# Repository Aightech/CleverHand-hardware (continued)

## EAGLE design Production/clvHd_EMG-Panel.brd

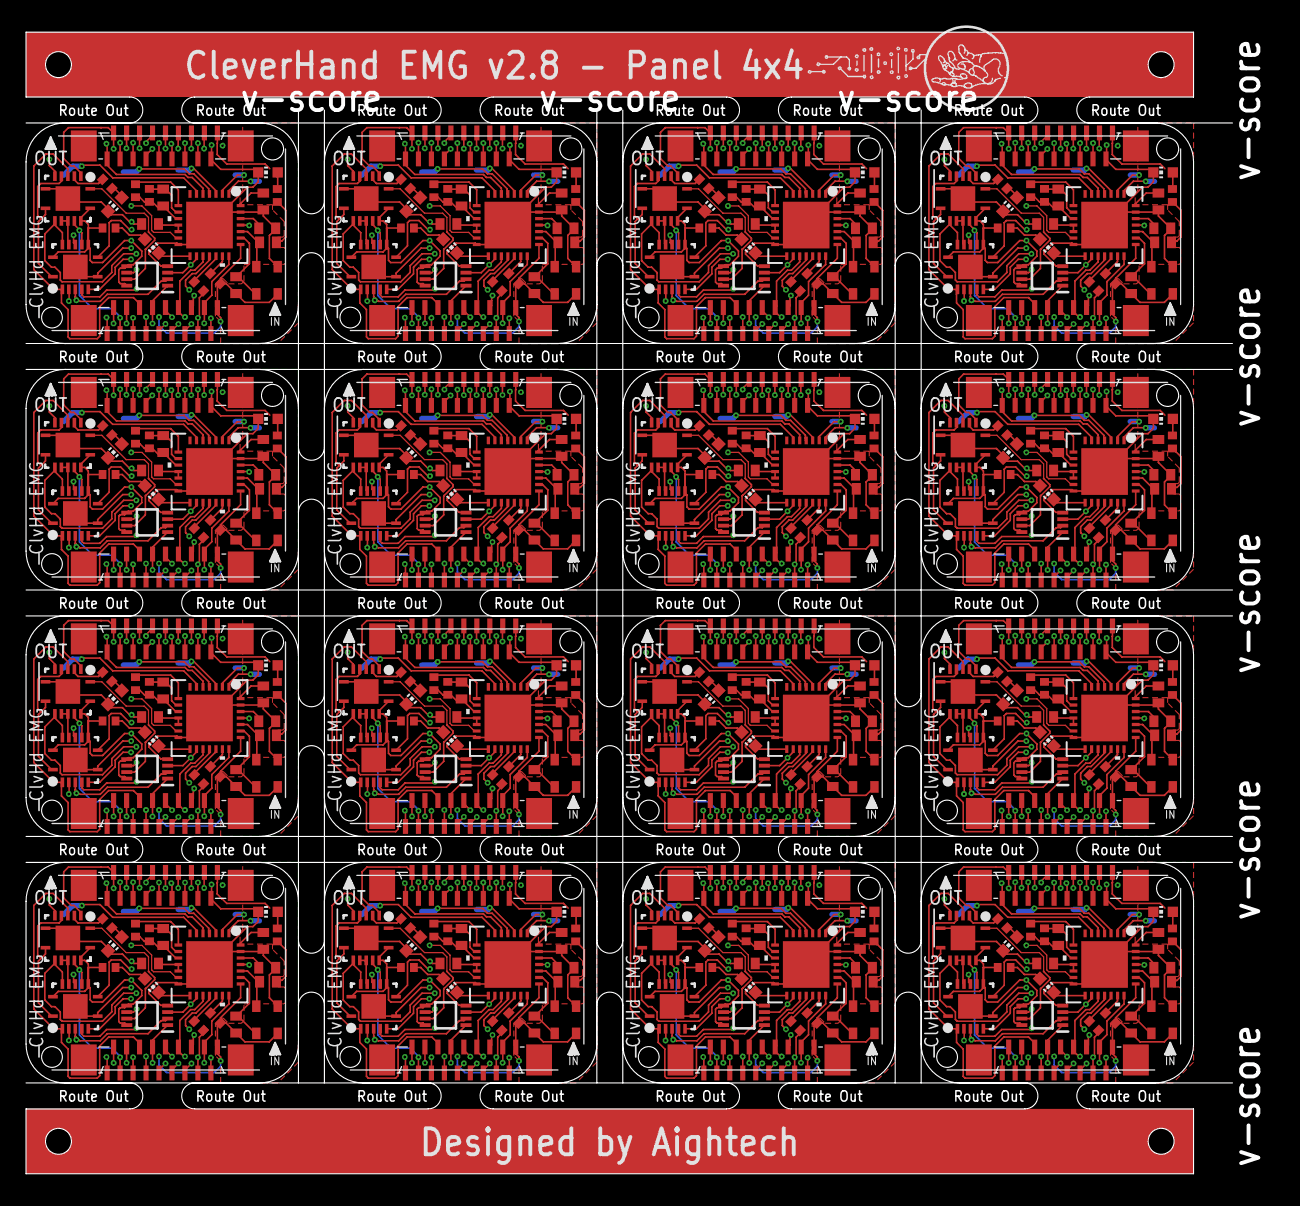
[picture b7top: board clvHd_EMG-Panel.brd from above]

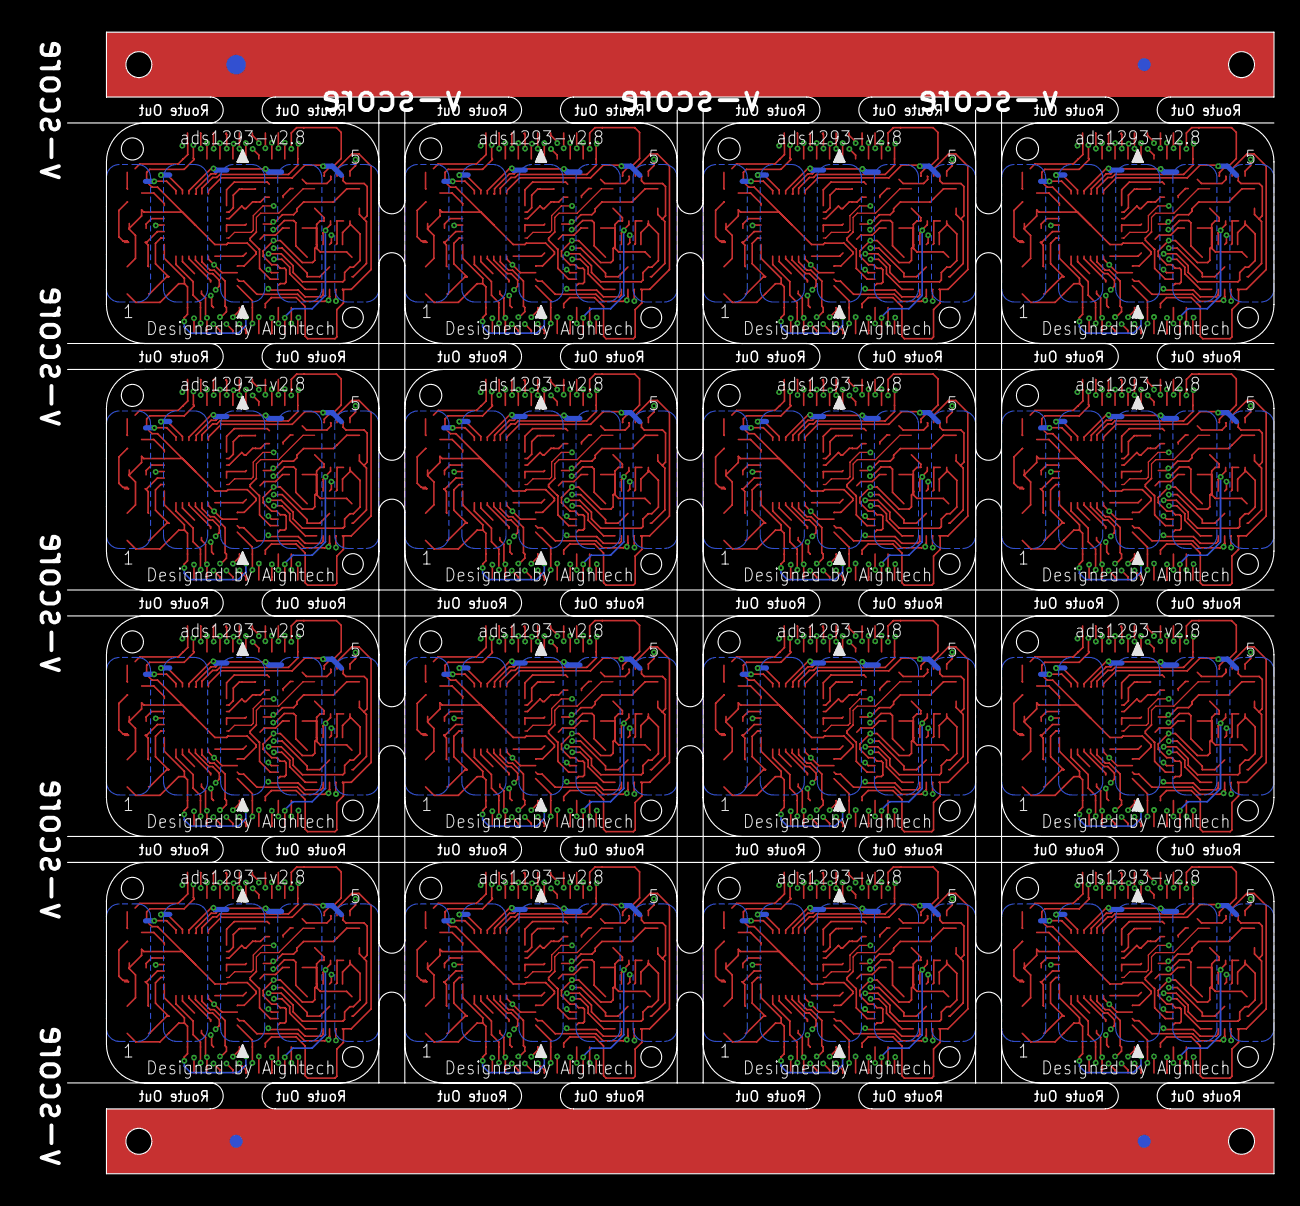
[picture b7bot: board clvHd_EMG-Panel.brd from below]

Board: 4 copper layers, 93.0 x 88.0 mm, 376 parts (4 on the bottom side), 592 nets.

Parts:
1, 2, 3, 4, 5, 6, 7, 8, 9, 10, 11, 12, 13, 14, 15, 16, 17, 18, 19, 20, 21, 22, 23, 24, 25, 26, 27, 28, 29, 30, 31, 32: X05C2018TZ
ADC, ADC1, ADC2, ADC3, ADC4, ADC5, ADC6, ADC7, ADC8, ADC9, ADC10, ADC11, ADC12, ADC13, ADC14, ADC15: ADS1293CISQ/NOPB; RSG28_3P6X3P6_TEX
C1, C2, C7, C8, C13, C14, C19, C20, C25, C26, C31, C32, C37, C38, C43, C44, C49, C50, C55, C56, C61, C62, C67, C68, C73, C74, C79, C80, C85, C86, C91, C92: 22pF; C0402
C3, C10, C16, C22, C28, C34, C40, C46, C52, C58, C64, C70, C76, C82, C88, C94: 1nF; C0402
C4, C5, C9, C11, C15, C17, C21, C23, C27, C29, C33, C35, C39, C41, C45, C47, C51, C53, C57, C59, C63, C65, C69, C71, C75, C77, C81, C83, C87, C89, C93, C95: 100nF; C0402
C6, C12, C18, C24, C30, C36, C42, C48, C54, C60, C66, C72, C78, C84, C90, C96: 1uF; C0402
E$1, E$2, E$3, E$4, E$5, E$6: FIDUCIAL-1X2
E$7, E$8: FIDUCIAL-1.5X3
L1, L5, L8, L11, L14, L17, L20, L23, L26, L29, L32, L35, L38, L41, L44, L47: Green; CHIP-LED0603
L2, L4, L7, L10, L13, L16, L19, L22, L25, L28, L31, L34, L37, L40, L43, L46: Red; CHIP-LED0603
L3, L6, L9, L12, L15, L18, L21, L24, L27, L30, L33, L36, L39, L42, L45, L48: White; CHIP-LED0603
L_AND, L_AND1, L_AND2, L_AND3, L_AND4, L_AND5, L_AND6, L_AND7, L_AND8, L_AND9, L_AND10, L_AND11, L_AND12, L_AND13, L_AND14, L_AND15: SN74ALVC08; VQFN-14-CUSTOM
L_NAND, L_NAND1, L_NAND2, L_NAND3, L_NAND4, L_NAND5, L_NAND6, L_NAND7, L_NAND8, L_NAND9, L_NAND10, L_NAND11, L_NAND12, L_NAND13, L_NAND14, L_NAND15: SN74AUP2G00; VSSOP
L_XOR, L_XOR1, L_XOR2, L_XOR3, L_XOR4, L_XOR5, L_XOR6, L_XOR7, L_XOR8, L_XOR9, L_XOR10, L_XOR11, L_XOR12, L_XOR13, L_XOR14, L_XOR15: SN74LVC86; VQFN-14-CUSTOM
R1, R2, R3, R4, R8, R9, R13, R14, R15, R16, R20, R21, R22, R23, R27, R28, R29, R30, R34, R35, R36, R37, R41, R42, R43, R44, R48, R49, R50, R51, R55, R56, R57, R58, R62, R63, R64, R65, R69, R70, R71, R72, R76, R77, R78, R79, R83, R84, R85, R86, R90, R91, R92, R93, R97, R98, R99, R100, R104, R105, R106, R107, R111, R112: 51; R0402
R5, R11, R18, R25, R32, R39, R46, R53, R60, R67, R74, R81, R88, R95, R102, R109: 10k; R0402
R6, R10, R17, R24, R31, R38, R45, R52, R59, R66, R73, R80, R87, R94, R101, R108: 1M; R0402
R7, R12, R19, R26, R33, R40, R47, R54, R61, R68, R75, R82, R89, R96, R103, R110: 10M; R0402
TAL, TAL1, TAL2, TAL3, TAL4, TAL5, TAL6, TAL7, TAL8, TAL9, TAL10, TAL11, TAL12, TAL13, TAL14, TAL15: C387328; SMD-3225_4P

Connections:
A0: 1.3, L_AND.12, L_XOR.10
A1: 1.5, L_AND.9, L_XOR.13
A2: 1.6, L_AND.4, L_XOR.2
A3: 1.8, L_NAND.1, L_XOR.5
A4: 4.5, L_AND1.9, L_XOR1.13
A5: 4.6, L_AND1.4, L_XOR1.2
A6: 4.8, L_NAND1.1, L_XOR1.5
A7: 4.3, L_AND1.12, L_XOR1.10
A8: 6.5, L_AND2.9, L_XOR2.13
A9: 6.6, L_AND2.4, L_XOR2.2
A10: 6.8, L_NAND2.1, L_XOR2.5
A11: 6.3, L_AND2.12, L_XOR2.10
A12: 8.5, L_AND3.9, L_XOR3.13
A13: 8.6, L_AND3.4, L_XOR3.2
A14: 8.8, L_NAND3.1, L_XOR3.5
A15: 8.3, L_AND3.12, L_XOR3.10
A16: 10.5, L_AND4.9, L_XOR4.13
A17: 10.6, L_AND4.4, L_XOR4.2
A18: 10.8, L_NAND4.1, L_XOR4.5
A19: 10.3, L_AND4.12, L_XOR4.10
A20: 12.5, L_AND5.9, L_XOR5.13
A21: 12.6, L_AND5.4, L_XOR5.2
A22: 12.8, L_NAND5.1, L_XOR5.5
A23: 12.3, L_AND5.12, L_XOR5.10
A24: 14.5, L_AND6.9, L_XOR6.13
A25: 14.6, L_AND6.4, L_XOR6.2
A26: 14.8, L_NAND6.1, L_XOR6.5
A27: 14.3, L_AND6.12, L_XOR6.10
A28: 16.5, L_AND7.9, L_XOR7.13
A29: 16.6, L_AND7.4, L_XOR7.2
A30: 16.8, L_NAND7.1, L_XOR7.5
A31: 16.3, L_AND7.12, L_XOR7.10
A32: 18.5, L_AND8.9, L_XOR8.13
A33: 18.6, L_AND8.4, L_XOR8.2
A34: 18.8, L_NAND8.1, L_XOR8.5
A35: 18.3, L_AND8.12, L_XOR8.10
A36: 20.5, L_AND9.9, L_XOR9.13
A37: 20.6, L_AND9.4, L_XOR9.2
A38: 20.8, L_NAND9.1, L_XOR9.5
A39: 20.3, L_AND9.12, L_XOR9.10
A40: 22.5, L_AND10.9, L_XOR10.13
A41: 22.6, L_AND10.4, L_XOR10.2
A42: 22.8, L_NAND10.1, L_XOR10.5
A43: 22.3, L_AND10.12, L_XOR10.10
A44: 24.5, L_AND11.9, L_XOR11.13
A45: 24.6, L_AND11.4, L_XOR11.2
A46: 24.8, L_NAND11.1, L_XOR11.5
A47: 24.3, L_AND11.12, L_XOR11.10
A48: 26.5, L_AND12.9, L_XOR12.13
A49: 26.6, L_AND12.4, L_XOR12.2
A50: 26.8, L_NAND12.1, L_XOR12.5
A51: 26.3, L_AND12.12, L_XOR12.10
A52: 28.5, L_AND13.9, L_XOR13.13
A53: 28.6, L_AND13.4, L_XOR13.2
A54: 28.8, L_NAND13.1, L_XOR13.5
A55: 28.3, L_AND13.12, L_XOR13.10
A56: 30.5, L_AND14.9, L_XOR14.13
A57: 30.6, L_AND14.4, L_XOR14.2
A58: 30.8, L_NAND14.1, L_XOR14.5
A59: 30.3, L_AND14.12, L_XOR14.10
A60: 32.5, L_AND15.9, L_XOR15.13
A61: 32.6, L_AND15.4, L_XOR15.2
A62: 32.8, L_NAND15.1, L_XOR15.5
A63: 32.3, L_AND15.12, L_XOR15.10
ALARMB: ADC.15, L2.C
ALARMB1: ADC1.15, L4.C
ALARMB2: ADC2.15, L7.C
ALARMB3: ADC3.15, L10.C
ALARMB4: ADC4.15, L13.C
ALARMB5: ADC5.15, L16.C
ALARMB6: ADC6.15, L19.C
ALARMB7: ADC7.15, L22.C
ALARMB8: ADC8.15, L25.C
ALARMB9: ADC9.15, L28.C
ALARMB10: ADC10.15, L31.C
ALARMB11: ADC11.15, L34.C
ALARMB12: ADC12.15, L37.C
ALARMB13: ADC13.15, L40.C
ALARMB14: ADC14.15, L43.C
ALARMB15: ADC15.15, L46.C
CLK: 1.16, 2.3, ADC.21
CLK1: 3.3, 4.16, ADC1.21
CLK2: 5.3, 6.16, ADC2.21
CLK3: 7.3, 8.16, ADC3.21
CLK4: 9.3, 10.16, ADC4.21
CLK5: 11.3, 12.16, ADC5.21
CLK6: 13.3, 14.16, ADC6.21
CLK7: 15.3, 16.16, ADC7.21
CLK8: 17.3, 18.16, ADC8.21
CLK9: 19.3, 20.16, ADC9.21
CLK10: 21.3, 22.16, ADC10.21
CLK11: 23.3, 24.16, ADC11.21
CLK12: 25.3, 26.16, ADC12.21
CLK13: 27.3, 28.16, ADC13.21
CLK14: 29.3, 30.16, ADC14.21
CLK15: 31.3, 32.16, ADC15.21
CMOUT: ADC.8, R5.1
CMOUT1: ADC1.8, R11.1
CMOUT2: ADC2.8, R18.1
CMOUT3: ADC3.8, R25.1
CMOUT4: ADC4.8, R32.1
CMOUT5: ADC5.8, R39.1
CMOUT6: ADC6.8, R46.1
CMOUT7: ADC7.8, R53.1
CMOUT8: ADC8.8, R60.1
CMOUT9: ADC9.8, R67.1
CMOUT10: ADC10.8, R74.1
CMOUT11: ADC11.8, R81.1
CMOUT12: ADC12.8, R88.1
CMOUT13: ADC13.8, R95.1
CMOUT14: ADC14.8, R102.1
CMOUT15: ADC15.8, R109.1
CS: ADC.16, L_NAND.3, L_NAND.6
CS1: ADC1.16, L_NAND1.3, L_NAND1.6
CS2: ADC2.16, L_NAND2.3, L_NAND2.6
CS3: ADC3.16, L_NAND3.3, L_NAND3.6
CS4: ADC4.16, L_NAND4.3, L_NAND4.6
CS5: ADC5.16, L_NAND5.3, L_NAND5.6
CS6: ADC6.16, L_NAND6.3, L_NAND6.6
CS7: ADC7.16, L_NAND7.3, L_NAND7.6
CS8: ADC8.16, L_NAND8.3, L_NAND8.6
CS9: ADC9.16, L_NAND9.3, L_NAND9.6
CS10: ADC10.16, L_NAND10.3, L_NAND10.6
CS11: ADC11.16, L_NAND11.3, L_NAND11.6
CS12: ADC12.16, L_NAND12.3, L_NAND12.6
CS13: ADC13.16, L_NAND13.3, L_NAND13.6
CS14: ADC14.16, L_NAND14.3, L_NAND14.6
CS15: ADC15.16, L_NAND15.3, L_NAND15.6
DIN: 1.13, 2.6, ADC.18
DIN1: 3.6, 4.13, ADC1.18
DIN2: 5.6, 6.13, ADC2.18
DIN3: 7.6, 8.13, ADC3.18
DIN4: 9.6, 10.13, ADC4.18
DIN5: 11.6, 12.13, ADC5.18
DIN6: 13.6, 14.13, ADC6.18
DIN7: 15.6, 16.13, ADC7.18
DIN8: 17.6, 18.13, ADC8.18
DIN9: 19.6, 20.13, ADC9.18
DIN10: 21.6, 22.13, ADC10.18
DIN11: 23.6, 24.13, ADC11.18
DIN12: 25.6, 26.13, ADC12.18
DIN13: 27.6, 28.13, ADC13.18
DIN14: 29.6, 30.13, ADC14.18
DIN15: 31.6, 32.13, ADC15.18
DOUT: 1.15, 2.4, R2.2
DOUT1: 3.4, 4.15, R8.2
DOUT2: 5.4, 6.15, R15.2
DOUT3: 7.4, 8.15, R22.2
DOUT4: 9.4, 10.15, R29.2
DOUT5: 11.4, 12.15, R36.2
DOUT6: 13.4, 14.15, R43.2
DOUT7: 15.4, 16.15, R50.2
DOUT8: 17.4, 18.15, R57.2
DOUT9: 19.4, 20.15, R64.2
DOUT10: 21.4, 22.15, R71.2
DOUT11: 23.4, 24.15, R78.2
DOUT12: 25.4, 26.15, R85.2
DOUT13: 27.4, 28.15, R92.2
DOUT14: 29.4, 30.15, R99.2
DOUT15: 31.4, 32.15, R106.2
DRDYB: ADC.20, R6.1
DRDYB1: ADC1.20, R10.1
DRDYB2: ADC2.20, R17.1
DRDYB3: ADC3.20, R24.1
DRDYB4: ADC4.20, R31.1
DRDYB5: ADC5.20, R38.1
DRDYB6: ADC6.20, R45.1
DRDYB7: ADC7.20, R52.1
DRDYB8: ADC8.20, R59.1
DRDYB9: ADC9.20, R66.1
DRDYB10: ADC10.20, R73.1
DRDYB11: ADC11.20, R80.1
DRDYB12: ADC12.20, R87.1
DRDYB13: ADC13.20, R94.1
DRDYB14: ADC14.20, R101.1
DRDYB15: ADC15.20, R108.1
GND: 1.4, 1.7, 1.11, 1.14, 1.17, 2.2, 2.5, 2.8, 2.12, 2.15, ADC.14, ADC.27, ADC.29, C4.2, C5.2, C6.2, L1.C, L3.C, L_AND.7, L_AND.15, L_NAND.4, L_XOR.7, L_XOR.15, TAL.2
GND1: 3.2, 3.5, 3.8, 3.12, 3.15, 4.4, 4.7, 4.11, 4.14, 4.17, ADC1.14, ADC1.27, ADC1.29, C9.2, C11.2, C12.2, L5.C, L6.C, L_AND1.7, L_AND1.15, L_NAND1.4, L_XOR1.7, L_XOR1.15, TAL1.2
GND2: 5.2, 5.5, 5.8, 5.12, 5.15, 6.4, 6.7, 6.11, 6.14, 6.17, ADC2.14, ADC2.27, ADC2.29, C15.2, C17.2, C18.2, L8.C, L9.C, L_AND2.7, L_AND2.15, L_NAND2.4, L_XOR2.7, L_XOR2.15, TAL2.2
GND3: 7.2, 7.5, 7.8, 7.12, 7.15, 8.4, 8.7, 8.11, 8.14, 8.17, ADC3.14, ADC3.27, ADC3.29, C21.2, C23.2, C24.2, L11.C, L12.C, L_AND3.7, L_AND3.15, L_NAND3.4, L_XOR3.7, L_XOR3.15, TAL3.2
GND4: 9.2, 9.5, 9.8, 9.12, 9.15, 10.4, 10.7, 10.11, 10.14, 10.17, ADC4.14, ADC4.27, ADC4.29, C27.2, C29.2, C30.2, L14.C, L15.C, L_AND4.7, L_AND4.15, L_NAND4.4, L_XOR4.7, L_XOR4.15, TAL4.2
GND5: 11.2, 11.5, 11.8, 11.12, 11.15, 12.4, 12.7, 12.11, 12.14, 12.17, ADC5.14, ADC5.27, ADC5.29, C33.2, C35.2, C36.2, L17.C, L18.C, L_AND5.7, L_AND5.15, L_NAND5.4, L_XOR5.7, L_XOR5.15, TAL5.2
GND6: 13.2, 13.5, 13.8, 13.12, 13.15, 14.4, 14.7, 14.11, 14.14, 14.17, ADC6.14, ADC6.27, ADC6.29, C39.2, C41.2, C42.2, L20.C, L21.C, L_AND6.7, L_AND6.15, L_NAND6.4, L_XOR6.7, L_XOR6.15, TAL6.2
GND7: 15.2, 15.5, 15.8, 15.12, 15.15, 16.4, 16.7, 16.11, 16.14, 16.17, ADC7.14, ADC7.27, ADC7.29, C45.2, C47.2, C48.2, L23.C, L24.C, L_AND7.7, L_AND7.15, L_NAND7.4, L_XOR7.7, L_XOR7.15, TAL7.2
GND8: 17.2, 17.5, 17.8, 17.12, 17.15, 18.4, 18.7, 18.11, 18.14, 18.17, ADC8.14, ADC8.27, ADC8.29, C51.2, C53.2, C54.2, L26.C, L27.C, L_AND8.7, L_AND8.15, L_NAND8.4, L_XOR8.7, L_XOR8.15, TAL8.2
GND9: 19.2, 19.5, 19.8, 19.12, 19.15, 20.4, 20.7, 20.11, 20.14, 20.17, ADC9.14, ADC9.27, ADC9.29, C57.2, C59.2, C60.2, L29.C, L30.C, L_AND9.7, L_AND9.15, L_NAND9.4, L_XOR9.7, L_XOR9.15, TAL9.2
GND10: 21.2, 21.5, 21.8, 21.12, 21.15, 22.4, 22.7, 22.11, 22.14, 22.17, ADC10.14, ADC10.27, ADC10.29, C63.2, C65.2, C66.2, L32.C, L33.C, L_AND10.7, L_AND10.15, L_NAND10.4, L_XOR10.7, L_XOR10.15, TAL10.2
GND11: 23.2, 23.5, 23.8, 23.12, 23.15, 24.4, 24.7, 24.11, 24.14, 24.17, ADC11.14, ADC11.27, ADC11.29, C69.2, C71.2, C72.2, L35.C, L36.C, L_AND11.7, L_AND11.15, L_NAND11.4, L_XOR11.7, L_XOR11.15, TAL11.2
GND12: 25.2, 25.5, 25.8, 25.12, 25.15, 26.4, 26.7, 26.11, 26.14, 26.17, ADC12.14, ADC12.27, ADC12.29, C75.2, C77.2, C78.2, L38.C, L39.C, L_AND12.7, L_AND12.15, L_NAND12.4, L_XOR12.7, L_XOR12.15, TAL12.2
GND13: 27.2, 27.5, 27.8, 27.12, 27.15, 28.4, 28.7, 28.11, 28.14, 28.17, ADC13.14, ADC13.27, ADC13.29, C81.2, C83.2, C84.2, L41.C, L42.C, L_AND13.7, L_AND13.15, L_NAND13.4, L_XOR13.7, L_XOR13.15, TAL13.2
GND14: 29.2, 29.5, 29.8, 29.12, 29.15, 30.4, 30.7, 30.11, 30.14, 30.17, ADC14.14, ADC14.27, ADC14.29, C87.2, C89.2, C90.2, L44.C, L45.C, L_AND14.7, L_AND14.15, L_NAND14.4, L_XOR14.7, L_XOR14.15, TAL14.2
GND15: 31.2, 31.5, 31.8, 31.12, 31.15, 32.4, 32.7, 32.11, 32.14, 32.17, ADC15.14, ADC15.27, ADC15.29, C93.2, C95.2, C96.2, L47.C, L48.C, L_AND15.7, L_AND15.15, L_NAND15.4, L_XOR15.7, L_XOR15.15, TAL15.2
GPIO1: 1.2, 2.17, L_AND.2
GPIO2: 3.17, 4.2, L_AND1.2
GPIO3: 5.17, 6.2, L_AND2.2
GPIO4: 7.17, 8.2, L_AND3.2
GPIO5: 9.17, 10.2, L_AND4.2
GPIO6: 11.17, 12.2, L_AND5.2
GPIO7: 13.17, 14.2, L_AND6.2
GPIO8: 15.17, 16.2, L_AND7.2
GPIO9: 17.17, 18.2, L_AND8.2
GPIO10: 19.17, 20.2, L_AND9.2
GPIO11: 21.17, 22.2, L_AND10.2
GPIO12: 23.17, 24.2, L_AND11.2
GPIO13: 25.17, 26.2, L_AND12.2
GPIO14: 27.17, 28.2, L_AND13.2
GPIO15: 29.17, 30.2, L_AND14.2
GPIO16: 31.17, 32.2, L_AND15.2
IN5: 1.1, 2.18, ADC.5
IN10: 3.18, 4.1, ADC1.5
IN16: 5.18, 6.1, ADC2.5
IN22: 7.18, 8.1, ADC3.5
IN28: 9.18, 10.1, ADC4.5
IN34: 11.18, 12.1, ADC5.5
IN40: 13.18, 14.1, ADC6.5
IN46: 15.18, 16.1, ADC7.5
IN52: 17.18, 18.1, ADC8.5
IN58: 19.18, 20.1, ADC9.5
IN64: 21.18, 22.1, ADC10.5
IN70: 23.18, 24.1, ADC11.5
IN76: 25.18, 26.1, ADC12.5
IN82: 27.18, 28.1, ADC13.5
IN88: 29.18, 30.1, ADC14.5
IN94: 31.18, 32.1, ADC15.5
unnamed: L_AND.1, L_NAND.7
unnamed: L1.A, R1.2
unnamed: ADC.19, R2.1
unnamed: ADC.23, C1.2, TAL.4
unnamed: L_AND.3, R3.2
unnamed: L2.A, R4.1
unnamed: L3.A, R3.1
unnamed: ADC.24, C2.2, TAL.3
unnamed: ADC.26, C6.1
unnamed: ADC1.19, R8.1
unnamed: L_AND.10, L_AND.11, L_XOR.12
unnamed: ADC1.23, C8.2, TAL1.4
unnamed: L_AND.5, L_AND.8, L_XOR.1
unnamed: ADC1.24, C7.2, TAL1.3
unnamed: ADC.10, C3.1, R5.2, R7.2
unnamed: L_AND.6, L_NAND.2, L_XOR.4
unnamed: ADC1.10, C10.1, R11.2, R12.2
unnamed: ADC1.26, C12.1
unnamed: L5.A, R13.2
unnamed: L4.A, R9.1
unnamed: L_AND1.3, R14.2
unnamed: L_AND1.6, L_NAND1.2, L_XOR1.4
unnamed: L_AND1.5, L_AND1.8, L_XOR1.1
unnamed: L_AND1.10, L_AND1.11, L_XOR1.12
unnamed: L_AND1.1, L_NAND1.7
unnamed: L6.A, R14.1
unnamed: ADC2.19, R15.1
unnamed: ADC2.23, C14.2, TAL2.4
unnamed: ADC2.24, C13.2, TAL2.3
unnamed: ADC2.10, C16.1, R18.2, R19.2
unnamed: ADC2.26, C18.1
unnamed: L8.A, R20.2
unnamed: L7.A, R16.1
unnamed: L_AND2.3, R21.2
unnamed: L_AND2.6, L_NAND2.2, L_XOR2.4
unnamed: L_AND2.5, L_AND2.8, L_XOR2.1
unnamed: L_AND2.10, L_AND2.11, L_XOR2.12
unnamed: L_AND2.1, L_NAND2.7
unnamed: L9.A, R21.1
unnamed: ADC3.19, R22.1
unnamed: ADC3.23, C20.2, TAL3.4
unnamed: ADC3.24, C19.2, TAL3.3
unnamed: ADC3.10, C22.1, R25.2, R26.2
unnamed: ADC3.26, C24.1
unnamed: L11.A, R27.2
unnamed: L10.A, R23.1
unnamed: L_AND3.3, R28.2
unnamed: L_AND3.6, L_NAND3.2, L_XOR3.4
unnamed: L_AND3.5, L_AND3.8, L_XOR3.1
unnamed: L_AND3.10, L_AND3.11, L_XOR3.12
unnamed: L_AND3.1, L_NAND3.7
unnamed: L12.A, R28.1
unnamed: ADC4.19, R29.1
unnamed: ADC4.23, C26.2, TAL4.4
unnamed: ADC4.24, C25.2, TAL4.3
unnamed: ADC4.10, C28.1, R32.2, R33.2
unnamed: ADC4.26, C30.1
unnamed: L14.A, R34.2
unnamed: L13.A, R30.1
unnamed: L_AND4.3, R35.2
unnamed: L_AND4.6, L_NAND4.2, L_XOR4.4
unnamed: L_AND4.5, L_AND4.8, L_XOR4.1
unnamed: L_AND4.10, L_AND4.11, L_XOR4.12
unnamed: L_AND4.1, L_NAND4.7
unnamed: L15.A, R35.1
unnamed: ADC5.19, R36.1
unnamed: ADC5.23, C32.2, TAL5.4
unnamed: ADC5.24, C31.2, TAL5.3
unnamed: ADC5.10, C34.1, R39.2, R40.2
unnamed: ADC5.26, C36.1
unnamed: L17.A, R41.2
unnamed: L16.A, R37.1
unnamed: L_AND5.3, R42.2
unnamed: L_AND5.6, L_NAND5.2, L_XOR5.4
unnamed: L_AND5.5, L_AND5.8, L_XOR5.1
unnamed: L_AND5.10, L_AND5.11, L_XOR5.12
unnamed: L_AND5.1, L_NAND5.7
unnamed: L18.A, R42.1
unnamed: ADC6.19, R43.1
unnamed: ADC6.23, C38.2, TAL6.4
unnamed: ADC6.24, C37.2, TAL6.3
unnamed: ADC6.10, C40.1, R46.2, R47.2
unnamed: ADC6.26, C42.1
unnamed: L20.A, R48.2
unnamed: L19.A, R44.1
unnamed: L_AND6.3, R49.2
unnamed: L_AND6.6, L_NAND6.2, L_XOR6.4
unnamed: L_AND6.5, L_AND6.8, L_XOR6.1
unnamed: L_AND6.10, L_AND6.11, L_XOR6.12
unnamed: L_AND6.1, L_NAND6.7
unnamed: L21.A, R49.1
unnamed: ADC7.19, R50.1
unnamed: ADC7.23, C44.2, TAL7.4
unnamed: ADC7.24, C43.2, TAL7.3
unnamed: ADC7.10, C46.1, R53.2, R54.2
unnamed: ADC7.26, C48.1
unnamed: L23.A, R55.2
unnamed: L22.A, R51.1
unnamed: L_AND7.3, R56.2
unnamed: L_AND7.6, L_NAND7.2, L_XOR7.4
unnamed: L_AND7.5, L_AND7.8, L_XOR7.1
unnamed: L_AND7.10, L_AND7.11, L_XOR7.12
unnamed: L_AND7.1, L_NAND7.7
unnamed: L24.A, R56.1
unnamed: ADC8.19, R57.1
unnamed: ADC8.23, C50.2, TAL8.4
unnamed: ADC8.24, C49.2, TAL8.3
unnamed: ADC8.10, C52.1, R60.2, R61.2
unnamed: ADC8.26, C54.1
unnamed: L26.A, R62.2
unnamed: L25.A, R58.1
unnamed: L_AND8.3, R63.2
unnamed: L_AND8.6, L_NAND8.2, L_XOR8.4
unnamed: L_AND8.5, L_AND8.8, L_XOR8.1
unnamed: L_AND8.10, L_AND8.11, L_XOR8.12
unnamed: L_AND8.1, L_NAND8.7
unnamed: L27.A, R63.1
unnamed: ADC9.19, R64.1
unnamed: ADC9.23, C56.2, TAL9.4
unnamed: ADC9.24, C55.2, TAL9.3
unnamed: ADC9.10, C58.1, R67.2, R68.2
unnamed: ADC9.26, C60.1
unnamed: L29.A, R69.2
unnamed: L28.A, R65.1
unnamed: L_AND9.3, R70.2
unnamed: L_AND9.6, L_NAND9.2, L_XOR9.4
unnamed: L_AND9.5, L_AND9.8, L_XOR9.1
unnamed: L_AND9.10, L_AND9.11, L_XOR9.12
unnamed: L_AND9.1, L_NAND9.7
unnamed: L30.A, R70.1
unnamed: ADC10.19, R71.1
unnamed: ADC10.23, C62.2, TAL10.4
unnamed: ADC10.24, C61.2, TAL10.3
unnamed: ADC10.10, C64.1, R74.2, R75.2
unnamed: ADC10.26, C66.1
unnamed: L32.A, R76.2
unnamed: L31.A, R72.1
unnamed: L_AND10.3, R77.2
unnamed: L_AND10.6, L_NAND10.2, L_XOR10.4
unnamed: L_AND10.5, L_AND10.8, L_XOR10.1
unnamed: L_AND10.10, L_AND10.11, L_XOR10.12
unnamed: L_AND10.1, L_NAND10.7
unnamed: L33.A, R77.1
unnamed: ADC11.19, R78.1
unnamed: ADC11.23, C68.2, TAL11.4
unnamed: ADC11.24, C67.2, TAL11.3
unnamed: ADC11.10, C70.1, R81.2, R82.2
unnamed: ADC11.26, C72.1
unnamed: L35.A, R83.2
unnamed: L34.A, R79.1
unnamed: L_AND11.3, R84.2
unnamed: L_AND11.6, L_NAND11.2, L_XOR11.4
unnamed: L_AND11.5, L_AND11.8, L_XOR11.1
unnamed: L_AND11.10, L_AND11.11, L_XOR11.12
unnamed: L_AND11.1, L_NAND11.7
unnamed: L36.A, R84.1
unnamed: ADC12.19, R85.1
unnamed: ADC12.23, C74.2, TAL12.4
unnamed: ADC12.24, C73.2, TAL12.3
unnamed: ADC12.10, C76.1, R88.2, R89.2
unnamed: ADC12.26, C78.1
unnamed: L38.A, R90.2
unnamed: L37.A, R86.1
unnamed: L_AND12.3, R91.2
unnamed: L_AND12.6, L_NAND12.2, L_XOR12.4
unnamed: L_AND12.5, L_AND12.8, L_XOR12.1
unnamed: L_AND12.10, L_AND12.11, L_XOR12.12
unnamed: L_AND12.1, L_NAND12.7
unnamed: L39.A, R91.1
unnamed: ADC13.19, R92.1
unnamed: ADC13.23, C80.2, TAL13.4
unnamed: ADC13.24, C79.2, TAL13.3
unnamed: ADC13.10, C82.1, R95.2, R96.2
unnamed: ADC13.26, C84.1
unnamed: L41.A, R97.2
unnamed: L40.A, R93.1
unnamed: L_AND13.3, R98.2
unnamed: L_AND13.6, L_NAND13.2, L_XOR13.4
unnamed: L_AND13.5, L_AND13.8, L_XOR13.1
unnamed: L_AND13.10, L_AND13.11, L_XOR13.12
unnamed: L_AND13.1, L_NAND13.7
unnamed: L42.A, R98.1
unnamed: ADC14.19, R99.1
unnamed: ADC14.23, C86.2, TAL14.4
unnamed: ADC14.24, C85.2, TAL14.3
unnamed: ADC14.10, C88.1, R102.2, R103.2
unnamed: ADC14.26, C90.1
unnamed: L44.A, R104.2
unnamed: L43.A, R100.1
unnamed: L_AND14.3, R105.2
unnamed: L_AND14.6, L_NAND14.2, L_XOR14.4
unnamed: L_AND14.5, L_AND14.8, L_XOR14.1
unnamed: L_AND14.10, L_AND14.11, L_XOR14.12
unnamed: L_AND14.1, L_NAND14.7
unnamed: L45.A, R105.1
unnamed: ADC15.19, R106.1
unnamed: ADC15.23, C92.2, TAL15.4
unnamed: ADC15.24, C91.2, TAL15.3
unnamed: ADC15.10, C94.1, R109.2, R110.2
unnamed: ADC15.26, C96.1
unnamed: L47.A, R111.2
unnamed: L46.A, R107.1
unnamed: L_AND15.3, R112.2
unnamed: L_AND15.6, L_NAND15.2, L_XOR15.4
unnamed: L_AND15.5, L_AND15.8, L_XOR15.1
unnamed: L_AND15.10, L_AND15.11, L_XOR15.12
unnamed: L_AND15.1, L_NAND15.7
unnamed: L48.A, R112.1
RLDOUT: ADC.9, C3.2, R7.1
RLDOUT1: ADC1.9, C10.2, R12.1
RLDOUT2: ADC2.9, C16.2, R19.1
RLDOUT3: ADC3.9, C22.2, R26.1
RLDOUT4: ADC4.9, C28.2, R33.1
RLDOUT5: ADC5.9, C34.2, R40.1
RLDOUT6: ADC6.9, C40.2, R47.1
RLDOUT7: ADC7.9, C46.2, R54.1
RLDOUT8: ADC8.9, C52.2, R61.1
RLDOUT9: ADC9.9, C58.2, R68.1
RLDOUT10: ADC10.9, C64.2, R75.1
RLDOUT11: ADC11.9, C70.2, R82.1
RLDOUT12: ADC12.9, C76.2, R89.1
RLDOUT13: ADC13.9, C82.2, R96.1
RLDOUT14: ADC14.9, C88.2, R103.1
RLDOUT15: ADC15.9, C94.2, R110.1
RLDREF: ADC.11, ADC.12, C5.1
RLDREF1: ADC1.11, ADC1.12, C9.1
RLDREF2: ADC2.11, ADC2.12, C15.1
RLDREF3: ADC3.11, ADC3.12, C21.1
RLDREF4: ADC4.11, ADC4.12, C27.1
RLDREF5: ADC5.11, ADC5.12, C33.1
RLDREF6: ADC6.11, ADC6.12, C39.1
RLDREF7: ADC7.11, ADC7.12, C45.1
RLDREF8: ADC8.11, ADC8.12, C51.1
RLDREF9: ADC9.11, ADC9.12, C57.1
RLDREF10: ADC10.11, ADC10.12, C63.1
RLDREF11: ADC11.11, ADC11.12, C69.1
RLDREF12: ADC12.11, ADC12.12, C75.1
RLDREF13: ADC13.11, ADC13.12, C81.1
RLDREF14: ADC14.11, ADC14.12, C87.1
RLDREF15: ADC15.11, ADC15.12, C93.1
RST: 1.9, 2.10, ADC.25
RST1: 3.10, 4.9, ADC1.25
RST2: 5.10, 6.9, ADC2.25
RST3: 7.10, 8.9, ADC3.25
RST4: 9.10, 10.9, ADC4.25
RST5: 11.10, 12.9, ADC5.25
RST6: 13.10, 14.9, ADC6.25
RST7: 15.10, 16.9, ADC7.25
RST8: 17.10, 18.9, ADC8.25
RST9: 19.10, 20.9, ADC9.25
RST10: 21.10, 22.9, ADC10.25
RST11: 23.10, 24.9, ADC11.25
RST12: 25.10, 26.9, ADC12.25
RST13: 27.10, 28.9, ADC13.25
RST14: 29.10, 30.9, ADC14.25
RST15: 31.10, 32.9, ADC15.25
S0: 2.16, L_XOR.8
S1: 2.14, L_XOR.11
S2: 2.13, L_XOR.3
S3: 2.11, L_XOR.6
S4: 3.16, L_XOR1.8
S5: 3.14, L_XOR1.11
S6: 3.13, L_XOR1.3
S7: 3.11, L_XOR1.6
S8: 5.16, L_XOR2.8
S9: 5.14, L_XOR2.11
S10: 5.13, L_XOR2.3
S11: 5.11, L_XOR2.6
S12: 7.16, L_XOR3.8
S13: 7.14, L_XOR3.11
S14: 7.13, L_XOR3.3
S15: 7.11, L_XOR3.6
S16: 9.16, L_XOR4.8
S17: 9.14, L_XOR4.11
S18: 9.13, L_XOR4.3
S19: 9.11, L_XOR4.6
S20: 11.16, L_XOR5.8
S21: 11.14, L_XOR5.11
S22: 11.13, L_XOR5.3
S23: 11.11, L_XOR5.6
S24: 13.16, L_XOR6.8
S25: 13.14, L_XOR6.11
S26: 13.13, L_XOR6.3
S27: 13.11, L_XOR6.6
S28: 15.16, L_XOR7.8
S29: 15.14, L_XOR7.11
S30: 15.13, L_XOR7.3
S31: 15.11, L_XOR7.6
S32: 17.16, L_XOR8.8
S33: 17.14, L_XOR8.11
S34: 17.13, L_XOR8.3
S35: 17.11, L_XOR8.6
S36: 19.16, L_XOR9.8
S37: 19.14, L_XOR9.11
S38: 19.13, L_XOR9.3
S39: 19.11, L_XOR9.6
S40: 21.16, L_XOR10.8
S41: 21.14, L_XOR10.11
S42: 21.13, L_XOR10.3
S43: 21.11, L_XOR10.6
S44: 23.16, L_XOR11.8
S45: 23.14, L_XOR11.11
S46: 23.13, L_XOR11.3
S47: 23.11, L_XOR11.6
S48: 25.16, L_XOR12.8
S49: 25.14, L_XOR12.11
S50: 25.13, L_XOR12.3
S51: 25.11, L_XOR12.6
S52: 27.16, L_XOR13.8
S53: 27.14, L_XOR13.11
S54: 27.13, L_XOR13.3
S55: 27.11, L_XOR13.6
S56: 29.16, L_XOR14.8
S57: 29.14, L_XOR14.11
S58: 29.13, L_XOR14.3
S59: 29.11, L_XOR14.6
S60: 31.16, L_XOR15.8
S61: 31.14, L_XOR15.11
S62: 31.13, L_XOR15.3
S63: 31.11, L_XOR15.6
SCLK: 1.12, 2.7, ADC.17
SCLK1: 3.7, 4.12, ADC1.17
SCLK2: 5.7, 6.12, ADC2.17
SCLK3: 7.7, 8.12, ADC3.17
SCLK4: 9.7, 10.12, ADC4.17
SCLK5: 11.7, 12.12, ADC5.17
SCLK6: 13.7, 14.12, ADC6.17
SCLK7: 15.7, 16.12, ADC7.17
SCLK8: 17.7, 18.12, ADC8.17
SCLK9: 19.7, 20.12, ADC9.17
SCLK10: 21.7, 22.12, ADC10.17
SCLK11: 23.7, 24.12, ADC11.17
SCLK12: 25.7, 26.12, ADC12.17
SCLK13: 27.7, 28.12, ADC13.17
SCLK14: 29.7, 30.12, ADC14.17
SCLK15: 31.7, 32.12, ADC15.17
SYNCB: 1.10, 2.9, ADC.13
SYNCB1: 3.9, 4.10, ADC1.13
SYNCB2: 5.9, 6.10, ADC2.13
SYNCB3: 7.9, 8.10, ADC3.13
SYNCB4: 9.9, 10.10, ADC4.13
SYNCB5: 11.9, 12.10, ADC5.13
SYNCB6: 13.9, 14.10, ADC6.13
SYNCB7: 15.9, 16.10, ADC7.13
SYNCB8: 17.9, 18.10, ADC8.13
SYNCB9: 19.9, 20.10, ADC9.13
SYNCB10: 21.9, 22.10, ADC10.13
SYNCB11: 23.9, 24.10, ADC11.13
SYNCB12: 25.9, 26.10, ADC12.13
SYNCB13: 27.9, 28.10, ADC13.13
SYNCB14: 29.9, 30.10, ADC14.13
SYNCB15: 31.9, 32.10, ADC15.13
VDD: 1.18, 2.1, ADC.22, ADC.28, C1.1, C2.1, C4.1, L_AND.13, L_AND.14, L_NAND.5, L_NAND.8, L_XOR.9, L_XOR.14, R1.1, R4.2, R6.2, TAL.1
VDD1: 3.1, 4.18, ADC1.22, ADC1.28, C7.1, C8.1, C11.1, L_AND1.13, L_AND1.14, L_NAND1.5, L_NAND1.8, L_XOR1.9, L_XOR1.14, R9.2, R10.2, R13.1, TAL1.1
VDD2: 5.1, 6.18, ADC2.22, ADC2.28, C13.1, C14.1, C17.1, L_AND2.13, L_AND2.14, L_NAND2.5, L_NAND2.8, L_XOR2.9, L_XOR2.14, R16.2, R17.2, R20.1, TAL2.1
VDD3: 7.1, 8.18, ADC3.22, ADC3.28, C19.1, C20.1, C23.1, L_AND3.13, L_AND3.14, L_NAND3.5, L_NAND3.8, L_XOR3.9, L_XOR3.14, R23.2, R24.2, R27.1, TAL3.1
VDD4: 9.1, 10.18, ADC4.22, ADC4.28, C25.1, C26.1, C29.1, L_AND4.13, L_AND4.14, L_NAND4.5, L_NAND4.8, L_XOR4.9, L_XOR4.14, R30.2, R31.2, R34.1, TAL4.1
VDD5: 11.1, 12.18, ADC5.22, ADC5.28, C31.1, C32.1, C35.1, L_AND5.13, L_AND5.14, L_NAND5.5, L_NAND5.8, L_XOR5.9, L_XOR5.14, R37.2, R38.2, R41.1, TAL5.1
VDD6: 13.1, 14.18, ADC6.22, ADC6.28, C37.1, C38.1, C41.1, L_AND6.13, L_AND6.14, L_NAND6.5, L_NAND6.8, L_XOR6.9, L_XOR6.14, R44.2, R45.2, R48.1, TAL6.1
VDD7: 15.1, 16.18, ADC7.22, ADC7.28, C43.1, C44.1, C47.1, L_AND7.13, L_AND7.14, L_NAND7.5, L_NAND7.8, L_XOR7.9, L_XOR7.14, R51.2, R52.2, R55.1, TAL7.1
VDD8: 17.1, 18.18, ADC8.22, ADC8.28, C49.1, C50.1, C53.1, L_AND8.13, L_AND8.14, L_NAND8.5, L_NAND8.8, L_XOR8.9, L_XOR8.14, R58.2, R59.2, R62.1, TAL8.1
VDD9: 19.1, 20.18, ADC9.22, ADC9.28, C55.1, C56.1, C59.1, L_AND9.13, L_AND9.14, L_NAND9.5, L_NAND9.8, L_XOR9.9, L_XOR9.14, R65.2, R66.2, R69.1, TAL9.1
VDD10: 21.1, 22.18, ADC10.22, ADC10.28, C61.1, C62.1, C65.1, L_AND10.13, L_AND10.14, L_NAND10.5, L_NAND10.8, L_XOR10.9, L_XOR10.14, R72.2, R73.2, R76.1, TAL10.1
VDD11: 23.1, 24.18, ADC11.22, ADC11.28, C67.1, C68.1, C71.1, L_AND11.13, L_AND11.14, L_NAND11.5, L_NAND11.8, L_XOR11.9, L_XOR11.14, R79.2, R80.2, R83.1, TAL11.1
VDD12: 25.1, 26.18, ADC12.22, ADC12.28, C73.1, C74.1, C77.1, L_AND12.13, L_AND12.14, L_NAND12.5, L_NAND12.8, L_XOR12.9, L_XOR12.14, R86.2, R87.2, R90.1, TAL12.1
VDD13: 27.1, 28.18, ADC13.22, ADC13.28, C79.1, C80.1, C83.1, L_AND13.13, L_AND13.14, L_NAND13.5, L_NAND13.8, L_XOR13.9, L_XOR13.14, R93.2, R94.2, R97.1, TAL13.1
VDD14: 29.1, 30.18, ADC14.22, ADC14.28, C85.1, C86.1, C89.1, L_AND14.13, L_AND14.14, L_NAND14.5, L_NAND14.8, L_XOR14.9, L_XOR14.14, R100.2, R101.2, R104.1, TAL14.1
VDD15: 31.1, 32.18, ADC15.22, ADC15.28, C91.1, C92.1, C95.1, L_AND15.13, L_AND15.14, L_NAND15.5, L_NAND15.8, L_XOR15.9, L_XOR15.14, R107.2, R108.2, R111.1, TAL15.1

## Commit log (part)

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2021-08-24 v7-panel
    smd0201
2021-08-24 panelized
2021-08-29 jst sh conn
2021-08-29 dim changed to be panalized 3x4
2021-08-30 add rdy and sync
2021-09-24 placement
2021-09-24 gnd-vdd common
2021-09-24 finished
2021-09-24 pics
2021-09-25 panelization
2021-09-25 component val + minor debug
2021-09-26 Create clvHd.s##
2021-09-26 3d rendering
2021-09-26 update colors + text
2021-09-27 correction led
2021-09-27 redesign
2021-10-28 Xtal fixed + logo
2021-10-29 animation
2021-11-08 added master FES EMG folders
2021-11-26 almost fully routed
2021-11-27 ready for prod
2021-11-30 master update
2021-11-30 refactor git
2021-12-14 shrinken
2021-12-16 dir indication + lvl3 gnd plane
2022-01-23 double gate nand
2022-01-27 socket design
2022-02-06 long board
2022-04-12 global setup
2022-04-12 partial routing
2022-04-12 almost completely routed
2022-04-12 fully routed + text
2022-04-12 bottom stop correction + bottom text
2022-06-26 visual mod
2022-07-01 nand new package
    changed the json package for a vssop package to make is easier to solder. updated README, docs and CAM
2022-07-02 panelization + datasheet
2022-07-06 added stl model
2022-07-06 license and co
2022-07-06 added some pics
2022-07-15 neopixel
2022-07-16 fixed position c4-r1
2022-07-31 fixed g00 pinout
2022-10-26 v3.0 on kicad
2022-10-28 finished v3
2022-10-31 fixed some panel bug for jlcpcb
2022-11-01 v3.1 fixed solder and paste mask and some via pos
2022-12-30 cleanup directory
2023-02-22 new module with hc32l110 and some extension board
2023-05-29 lot of modification, preparing a refactor + some rendering
2023-09-08 updated bridge
2023-09-13 updated bridge board
2023-09-14 cleanup
2023-11-15 new version logicGate+hc32l to mitigate CS speed while keeping new features
2023-11-28 new modules EMGDAQ and COMMOD
2023-11-30 reshaped the modules boards sizes
2023-11-30 blender module assembly
2023-12-05 some cleaning + edge plating dry electrode
2023-12-05 some rendring
2023-12-07 finished rooting emgdaq + schematic commod
2023-12-30 lot of updates on ads93,flex,commod,pad
2024-01-02 finished ads93,commod,drypad,flexpad,jackconn,imubno + plot and render
2024-03-29 INA331 IMUICM
2024-03-29 jack, dry electrode
2024-03-30 refactor and fixing most of the modules
2024-03-30 new dry flex
2024-03-30 cleaned all modules + production files
2024-03-31 lot of rendering and documentaion
2024-04-01 fixed INA331 wrong package and add ext ref
2024-04-01 regenerated production files for INA331
2024-04-01 cleaned kicad folder
2024-04-01 renamed stl files
2024-04-17 renamed SPI buses
2024-06-24 fixed COM_MOD grounding issues
2024-07-02 Rename pinout2.png to initialisation/pinout2.png
2024-07-18 added progress state of the submodules
2024-07-28 minor update: added pins to access i2c pins of the com bus
2024-07-28 major update: fixed inversion of i2c lines + added pull up resistors + rotated 180deg fpc conector
2024-07-29 fixed ref number of FPC connectors and added ref numbers of resitors
2024-08-17 modified pins to expose in6 and gnd for potential filtering
2024-08-17 increase size of the board to make it easier to screw
2024-08-17 new dry electectrodes for ads1295 module
2024-08-17 pannel for new dry electrodes
2024-08-25 v3.2 fixed issue between GND and GNDA
2024-08-26 update production files of shield controller teensy
2024-09-02 mono controller, to have module working on their own and comunicate via wifi
2024-09-02 finished mono moudule, should be ready for manufacture
2024-09-02 fixed pico controller shield to match v3 modules
2024-09-02 minor fix on teensy shield
2024-09-03 fixed MONOCOM ERC and DRC: via size, missing pins
2024-09-04 generated production files and plots of controllers shield and mono ctrl
2024-10-08 added 2x2 panels for COM_MOD and EMD_ADS1293
2024-10-12 fixed castelated holes for beter fixation on interface board
2024-10-12 added mid size to fit better with ads1293 module and standad xtal + some modificaion
2024-10-12 minor graphical changes
2024-10-12 added some docs
2024-10-12 added doc and regenerated gerbers
2025-03-25 added esp32c3xiaoshield
2025-03-25 some work on mono controller
2026-01-04 refactoring and redocumenting all modules
2026-01-12 fixed readme
